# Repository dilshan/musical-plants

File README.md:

# CoCA Emerge + Tech - Musical plants project

[CoCA](http://www.cocaartists.com) "Emerge + Tech" - Musical plants is an electronics, software and plants base exhibit we initially developed for [Cinnamon Colomboscope](http://www.cinnamoncolomboscope.com/) 2016 exhibition. This installation will feature a touch sensitive sensor that will generate a soothing sound from each plant. By interacting with individual plants, the audience can create musical compositions.

Sensor unit of this project consists with 14 high sensitive, configurable voltage detectors and USB interface. In this sensor unit we use Samsung's KA2284 as amplifier, level detector, and PIC18F4550 8-bit MCU as data multiplexer and USB I/O controller. PC817 opto isolators are used to interface between analog front-end and digital data processor. In this design both analog and digital circuits are physically and electronically isolated to minimize the noises and interferences.

### Compiling source code

PC application of this project is developed by using [HIDAPI](https://github.com/signal11/hidapi) and [irrKlang](http://www.ambiera.com/irrklang) libraries. This application is designed to work with <I>Microsoft Windows</I> operating systems and we tested it on Windows 7 and Windows 10. 

PC application of this project is developed using <I>Microsoft Visual C++ 2015</I> edition. To compile the application <I>HIDAPI</I> and <I>irrKlang</I> source codes and libraries are need to copy into \frontend directory. 

PIC18F4550 firmware is developed using <I>MikroElektronika's mikroC PRO for PIC</I> compiler. Recommended MCU configuration register values for this firmware is listed in below:

* PLL prescaler : /5 (20 MHz)
* System clock postscaler : /2 (/1)
* USB clock : 96 MHz PLL /2
* Osciliator : HSPLL
* Fail safe clock monitor : OFF
* Internal external switching : OFF
* Power-up timer : OFF
* Brown-out reset : OFF
* Brown-out reset voltage : 2.0V
* USB voltage regulator : ON
* Watchdog timer : OFF
* Watchdog timer postscaler : 1:32768
* CCP2 multiplexed with : RC1
* PortB reset state : Digital
* Low power timer 1 osc : High power
* MCLR pin : Reset
* Stack overflow / underflow : ON
* In-circuit port : OFF
* Enhanced CPU : OFF
* Boot block : OPEN
* Code lock : OPEN
* Data EEPROM : OPEN
* Table write boot block : OPEN
* Table write code : OPEN
* Table read boot block : OPEN
* Table read code : OPEN

### Licenses

All the audio clips used in this project are produced by using xylophone and released under the terms of [Creative Commons Attribution-ShareAlike 4.0 International License](https://creativecommons.org/licenses/by-sa/4.0) (CC BY-SA 4.0).

This musical plants project is an open source hardware project and all the source codes and compiled binaries are released under the [MIT Licenses](https://opensource.org/licenses/MIT).

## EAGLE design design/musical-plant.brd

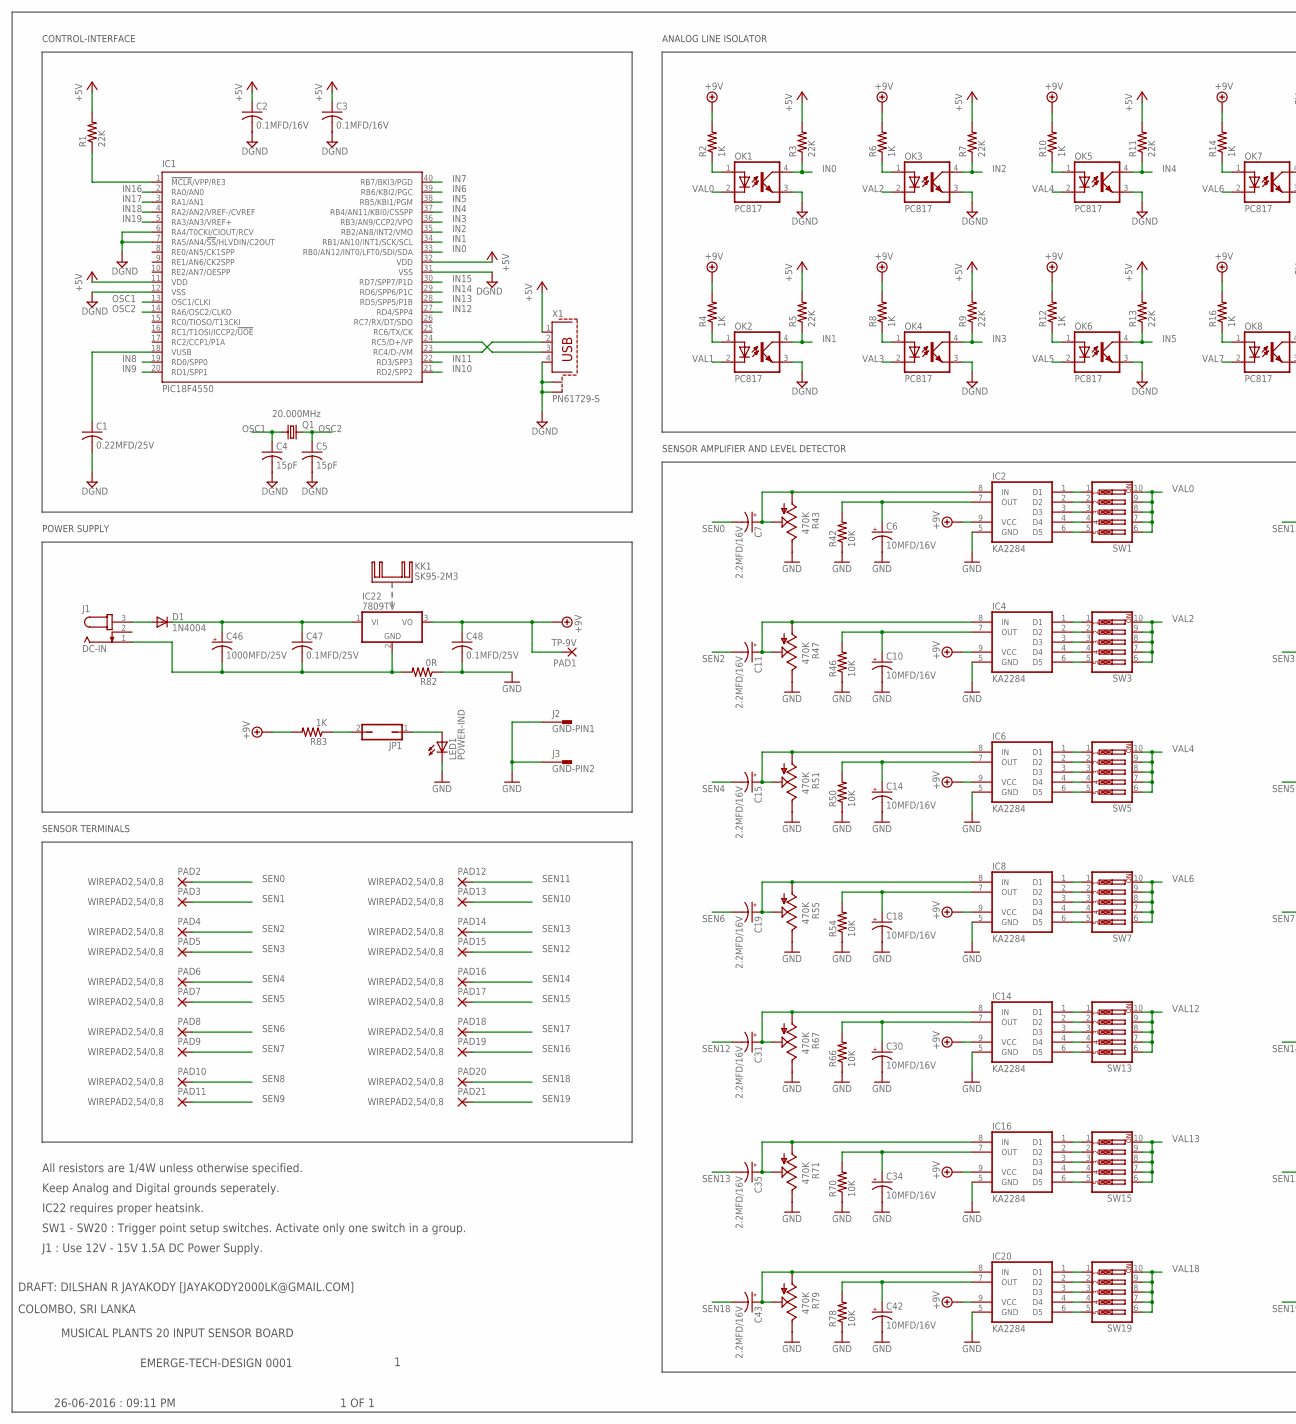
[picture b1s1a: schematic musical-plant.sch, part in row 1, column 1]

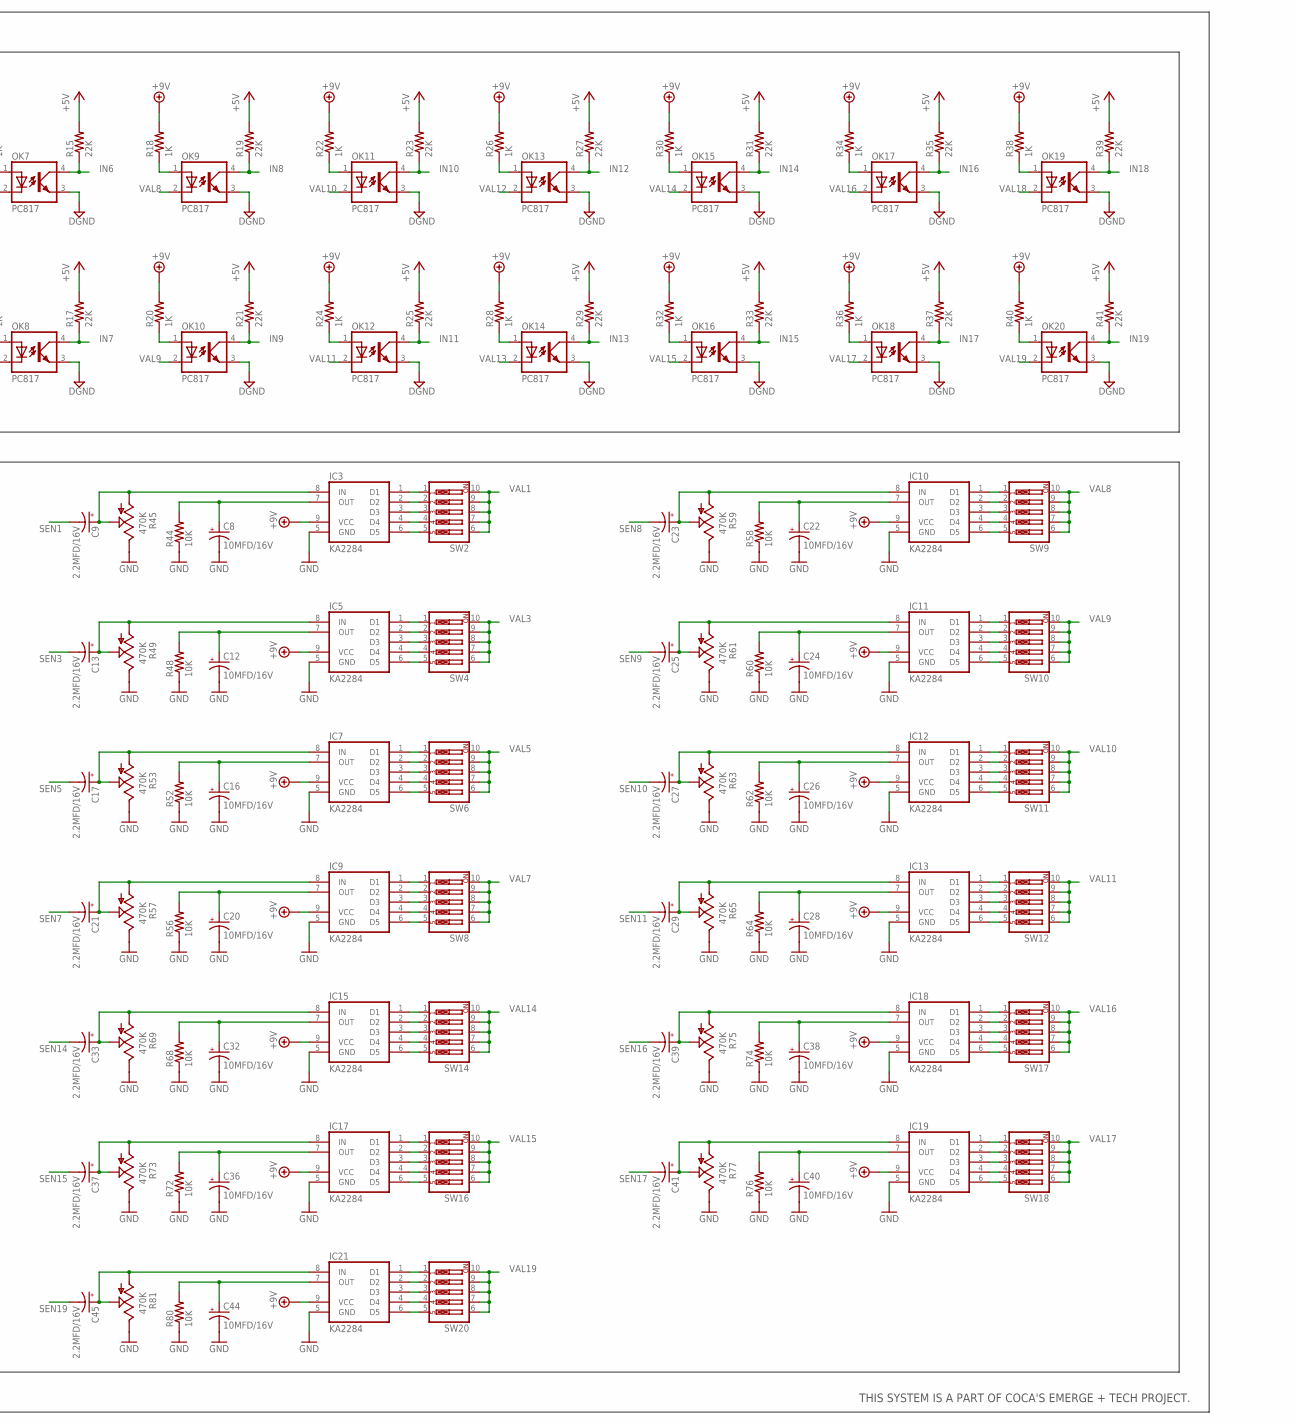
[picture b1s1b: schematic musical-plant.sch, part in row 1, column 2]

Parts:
C1: 0.22MFD/25V; C075-052X106
C2, C3: 0.1MFD/16V; C050-030X075
C4, C5: 15pF; C025-025X050
C6, C8, C10, C12, C14, C16, C18, C20, C22, C24, C26, C28, C30, C32, C34, C36, C38, C40, C42, C44: 10MFD/16V; E2,5-6E
C7, C9, C11, C13, C15, C17, C19, C21, C23, C25, C27, C29, C31, C33, C35, C37, C39, C41, C43, C45: 2.2MFD/16V; E2,5-6E
C46: 1000MFD/25V; E5-13
C47, C48: 0.1MFD/25V; C075-052X106
D1: 1N4004; DO41-10
IC1: PIC18F4550; DIL40
IC2, IC3, IC4, IC5, IC6, IC7, IC8, IC9, IC10, IC11, IC12, IC13, IC14, IC15, IC16, IC17, IC18, IC19, IC20, IC21: KA2284; SIP-9
IC22: 7809TV; TO220V
J1: DC-IN; SPC4078
J2: GND-PIN1; F061.080
J3: GND-PIN2; F061.080
JP1: JP1Q; JP1
KK1: SK95-2M3
LED1: POWER-IND; LED3MM
OK1, OK2, OK3, OK4, OK5, OK6, OK7, OK8, OK9, OK10, OK11, OK12, OK13, OK14, OK15, OK16, OK17, OK18, OK19, OK20: PC817; DIL04
PAD1: TP-9V; 2,15/1,0
PAD2, PAD3, PAD4, PAD5, PAD6, PAD7, PAD8, PAD9, PAD10, PAD11, PAD12, PAD13, PAD14, PAD15, PAD16, PAD17, PAD18, PAD19, PAD20, PAD21: WIREPAD2,54/0,8; 2,54/0,8
Q1: 20.000MHz; HC49/S
R1: 22K; 0207/10
R2, R4, R6, R8, R10, R12, R14, R16, R18, R20, R22, R24, R26, R28, R30, R32, R34, R36, R38, R40, R83: 1K; 0207/10
R3, R5, R7, R9, R11, R13, R15, R17, R19, R21, R23, R25, R27, R29, R31, R33, R35, R37, R39, R41: 22K; 0207/15
R42, R44, R46, R48, R50, R52, R54, R56, R58, R60, R62, R64, R66, R68, R70, R72, R74, R76, R78, R80: 10K; 0207/10
R43, R45, R47, R49, R51, R53, R55, R57, R59, R61, R63, R65, R67, R69, R71, R73, R75, R77, R79, R81: 470K; RS3
R82: 0R; 0207/10
SW1, SW2, SW3, SW4, SW5, SW6, SW7, SW8, SW9, SW10, SW11, SW12, SW13, SW14, SW15, SW16, SW17, SW18, SW19, SW20: SW_DIP-5; EDG-05
X1: PN61729-S

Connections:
+5V: C2.1, C3.1, IC1.11 (VDD), IC1.32 (VDD), R1.2, R3.2, R5.2, R7.2, R9.2, R11.2, R13.2, R15.2, R17.2, R19.2, R21.2, R23.2, R25.2, R27.2, R29.2, R31.2, R33.2, R35.2, R37.2, R39.2, R41.2, X1.1
+9V: C48.1, IC2.9 (VCC), IC3.9 (VCC), IC4.9 (VCC), IC5.9 (VCC), IC6.9 (VCC), IC7.9 (VCC), IC8.9 (VCC), IC9.9 (VCC), IC10.9 (VCC), IC11.9 (VCC), IC12.9 (VCC), IC13.9 (VCC), IC14.9 (VCC), IC15.9 (VCC), IC16.9 (VCC), IC17.9 (VCC), IC18.9 (VCC), IC19.9 (VCC), IC20.9 (VCC), IC21.9 (VCC), IC22.3 (VO), PAD1.1, R2.2, R4.2, R6.2, R8.2, R10.2, R12.2, R14.2, R16.2, R18.2, R20.2, R22.2, R24.2, R26.2, R28.2, R30.2, R32.2, R34.2, R36.2, R38.2, R40.2, R83.2
D-MINUS: IC1.23 (RC4/D-/VM), X1.2
D-PLUS: IC1.24 (RC5/D+/VP), X1.3
DGND: C1.2, C2.2, C3.2, C4.2, C5.2, IC1.6 (RA4/T0CKI/CIOUT/RCV), IC1.7 (RA5/AN4/!SS!/HLVDIN/C2OUT), IC1.12 (VSS), IC1.31 (VSS), OK1.3 (EMIT), OK2.3 (EMIT), OK3.3 (EMIT), OK4.3 (EMIT), OK5.3 (EMIT), OK6.3 (EMIT), OK7.3 (EMIT), OK8.3 (EMIT), OK9.3 (EMIT), OK10.3 (EMIT), OK11.3 (EMIT), OK12.3 (EMIT), OK13.3 (EMIT), OK14.3 (EMIT), OK15.3 (EMIT), OK16.3 (EMIT), OK17.3 (EMIT), OK18.3 (EMIT), OK19.3 (EMIT), OK20.3 (EMIT), X1.4, X1.S1, X1.S2
GND: C6.-, C8.-, C10.-, C12.-, C14.-, C16.-, C18.-, C20.-, C22.-, C24.-, C26.-, C28.-, C30.-, C32.-, C34.-, C36.-, C38.-, C40.-, C42.-, C44.-, C48.2, IC2.5 (GND), IC3.5 (GND), IC4.5 (GND), IC5.5 (GND), IC6.5 (GND), IC7.5 (GND), IC8.5 (GND), IC9.5 (GND), IC10.5 (GND), IC11.5 (GND), IC12.5 (GND), IC13.5 (GND), IC14.5 (GND), IC15.5 (GND), IC16.5 (GND), IC17.5 (GND), IC18.5 (GND), IC19.5 (GND), IC20.5 (GND), IC21.5 (GND), J2.1A, J2.1B, J3.1A, J3.1B, LED1.K (C), R42.1, R43.E, R44.1, R45.E, R46.1, R47.E, R48.1, R49.E, R50.1, R51.E, R52.1, R53.E, R54.1, R55.E, R56.1, R57.E, R58.1, R59.E, R60.1, R61.E, R62.1, R63.E, R64.1, R65.E, R66.1, R67.E, R68.1, R69.E, R70.1, R71.E, R72.1, R73.E, R74.1, R75.E, R76.1, R77.E, R78.1, R79.E, R80.1, R81.E, R82.1
IN0: IC1.33 (RB0/AN12/INT0/LFT0/SDI/SDA), OK1.4 (COL), R3.1
IN1: IC1.34 (RB1/AN10/INT1/SCK/SCL), OK2.4 (COL), R5.1
IN2: IC1.35 (RB2/AN8/INT2/VMO), OK3.4 (COL), R7.1
IN3: IC1.36 (RB3/AN9/CCP2/VPO), OK4.4 (COL), R9.1
IN4: IC1.37 (RB4/AN11/KBI0/CSSPP), OK5.4 (COL), R11.1
IN5: IC1.38 (RB5/KBI1/PGM), OK6.4 (COL), R13.1
IN6: IC1.39 (RB6/KBI2/PGC), OK7.4 (COL), R15.1
IN7: IC1.40 (RB7/BKI3/PGD), OK8.4 (COL), R17.1
IN8: IC1.19 (RD0/SPP0), OK9.4 (COL), R19.1
IN9: IC1.20 (RD1/SPP1), OK10.4 (COL), R21.1
IN10: IC1.21 (RD2/SPP2), OK11.4 (COL), R23.1
IN11: IC1.22 (RD3/SPP3), OK12.4 (COL), R25.1
IN12: IC1.27 (RD4/SPP4), OK13.4 (COL), R27.1
IN13: IC1.28 (RD5/SPP5/P1B), OK14.4 (COL), R29.1
IN14: IC1.29 (RD6/SPP6/P1C), OK15.4 (COL), R31.1
IN15: IC1.30 (RD7/SPP7/P1D), OK16.4 (COL), R33.1
IN16: IC1.2 (RA0/AN0), OK17.4 (COL), R35.1
IN17: IC1.3 (RA1/AN1), OK18.4 (COL), R37.1
IN18: IC1.4 (RA2/AN2/VREF-/CVREF), OK19.4 (COL), R39.1
IN19: IC1.5 (RA3/AN3/VREF+), OK20.4 (COL), R41.1
MCLR: IC1.1 (!MCLR!/VPP/RE3), R1.1
unnamed: OK1.1 (A), R2.1
unnamed: OK2.1 (A), R4.1
unnamed: OK3.1 (A), R6.1
unnamed: OK4.1 (A), R8.1
unnamed: OK5.1 (A), R10.1
unnamed: OK6.1 (A), R12.1
unnamed: OK7.1 (A), R14.1
unnamed: OK8.1 (A), R16.1
unnamed: OK9.1 (A), R18.1
unnamed: OK10.1 (A), R20.1
unnamed: OK11.1 (A), R22.1
unnamed: OK12.1 (A), R24.1
unnamed: OK13.1 (A), R26.1
unnamed: OK14.1 (A), R28.1
unnamed: OK15.1 (A), R30.1
unnamed: OK16.1 (A), R32.1
unnamed: OK17.1 (A), R34.1
unnamed: OK18.1 (A), R36.1
unnamed: OK19.1 (A), R38.1
unnamed: OK20.1 (A), R40.1
unnamed: IC2.1 (D1), SW1.1
unnamed: IC2.2 (D2), SW1.2
unnamed: IC2.3 (D3), SW1.3
unnamed: IC2.4 (D4), SW1.4
unnamed: IC2.6 (D5), SW1.5
unnamed: C6.+, IC2.7 (OUT), R42.2
unnamed: C7.+, IC2.8 (IN), R43.A, R43.S
unnamed: IC3.1 (D1), SW2.1
unnamed: IC3.2 (D2), SW2.2
unnamed: IC3.3 (D3), SW2.3
unnamed: IC3.4 (D4), SW2.4
unnamed: IC3.6 (D5), SW2.5
unnamed: C8.+, IC3.7 (OUT), R44.2
unnamed: C9.+, IC3.8 (IN), R45.A, R45.S
unnamed: IC4.1 (D1), SW3.1
unnamed: IC4.2 (D2), SW3.2
unnamed: IC4.3 (D3), SW3.3
unnamed: IC4.4 (D4), SW3.4
unnamed: IC4.6 (D5), SW3.5
unnamed: C10.+, IC4.7 (OUT), R46.2
unnamed: C11.+, IC4.8 (IN), R47.A, R47.S
unnamed: IC5.1 (D1), SW4.1
unnamed: IC5.2 (D2), SW4.2
unnamed: IC5.3 (D3), SW4.3
unnamed: IC5.4 (D4), SW4.4
unnamed: IC5.6 (D5), SW4.5
unnamed: C12.+, IC5.7 (OUT), R48.2
unnamed: C13.+, IC5.8 (IN), R49.A, R49.S
unnamed: IC6.1 (D1), SW5.1
unnamed: IC6.2 (D2), SW5.2
unnamed: IC6.3 (D3), SW5.3
unnamed: IC6.4 (D4), SW5.4
unnamed: IC6.6 (D5), SW5.5
unnamed: C14.+, IC6.7 (OUT), R50.2
unnamed: C15.+, IC6.8 (IN), R51.A, R51.S
unnamed: IC7.1 (D1), SW6.1
unnamed: IC7.2 (D2), SW6.2
unnamed: IC7.3 (D3), SW6.3
unnamed: IC7.4 (D4), SW6.4
unnamed: IC7.6 (D5), SW6.5
unnamed: C16.+, IC7.7 (OUT), R52.2
unnamed: C17.+, IC7.8 (IN), R53.A, R53.S
unnamed: IC8.1 (D1), SW7.1
unnamed: IC8.2 (D2), SW7.2
unnamed: IC8.3 (D3), SW7.3
unnamed: IC8.4 (D4), SW7.4
unnamed: IC8.6 (D5), SW7.5
unnamed: C18.+, IC8.7 (OUT), R54.2
unnamed: C19.+, IC8.8 (IN), R55.A, R55.S
unnamed: IC9.1 (D1), SW8.1
unnamed: IC9.2 (D2), SW8.2
unnamed: IC9.3 (D3), SW8.3
unnamed: IC9.4 (D4), SW8.4
unnamed: IC9.6 (D5), SW8.5
unnamed: C20.+, IC9.7 (OUT), R56.2
unnamed: C21.+, IC9.8 (IN), R57.A, R57.S
unnamed: IC10.1 (D1), SW9.1
unnamed: IC10.2 (D2), SW9.2
unnamed: IC10.3 (D3), SW9.3
unnamed: IC10.4 (D4), SW9.4
unnamed: IC10.6 (D5), SW9.5
unnamed: C22.+, IC10.7 (OUT), R58.2
unnamed: C23.+, IC10.8 (IN), R59.A, R59.S
unnamed: IC11.1 (D1), SW10.1
unnamed: IC11.2 (D2), SW10.2
unnamed: IC11.3 (D3), SW10.3
unnamed: IC11.4 (D4), SW10.4
unnamed: IC11.6 (D5), SW10.5
unnamed: C24.+, IC11.7 (OUT), R60.2
unnamed: C25.+, IC11.8 (IN), R61.A, R61.S
unnamed: IC12.1 (D1), SW11.1
unnamed: IC12.2 (D2), SW11.2
unnamed: IC12.3 (D3), SW11.3
unnamed: IC12.4 (D4), SW11.4
unnamed: IC12.6 (D5), SW11.5
unnamed: C26.+, IC12.7 (OUT), R62.2
unnamed: C27.+, IC12.8 (IN), R63.A, R63.S
unnamed: IC13.1 (D1), SW12.1
unnamed: IC13.2 (D2), SW12.2
unnamed: IC13.3 (D3), SW12.3
unnamed: IC13.4 (D4), SW12.4
unnamed: IC13.6 (D5), SW12.5
unnamed: C28.+, IC13.7 (OUT), R64.2
unnamed: C29.+, IC13.8 (IN), R65.A, R65.S
unnamed: IC14.1 (D1), SW13.1
unnamed: IC14.2 (D2), SW13.2
unnamed: IC14.3 (D3), SW13.3
unnamed: IC14.4 (D4), SW13.4
unnamed: IC14.6 (D5), SW13.5
unnamed: C30.+, IC14.7 (OUT), R66.2
unnamed: C31.+, IC14.8 (IN), R67.A, R67.S
unnamed: IC15.1 (D1), SW14.1
unnamed: IC15.2 (D2), SW14.2
unnamed: IC15.3 (D3), SW14.3
unnamed: IC15.4 (D4), SW14.4
unnamed: IC15.6 (D5), SW14.5
unnamed: C32.+, IC15.7 (OUT), R68.2
unnamed: C33.+, IC15.8 (IN), R69.A, R69.S
unnamed: IC16.1 (D1), SW15.1
unnamed: IC16.2 (D2), SW15.2
unnamed: IC16.3 (D3), SW15.3
unnamed: IC16.4 (D4), SW15.4
unnamed: IC16.6 (D5), SW15.5
unnamed: C34.+, IC16.7 (OUT), R70.2
unnamed: C35.+, IC16.8 (IN), R71.A, R71.S
unnamed: IC17.1 (D1), SW16.1
unnamed: IC17.2 (D2), SW16.2
unnamed: IC17.3 (D3), SW16.3
unnamed: IC17.4 (D4), SW16.4
unnamed: IC17.6 (D5), SW16.5
unnamed: C36.+, IC17.7 (OUT), R72.2
unnamed: C37.+, IC17.8 (IN), R73.A, R73.S
unnamed: IC18.1 (D1), SW17.1
unnamed: IC18.2 (D2), SW17.2
unnamed: IC18.3 (D3), SW17.3
unnamed: IC18.4 (D4), SW17.4
unnamed: IC18.6 (D5), SW17.5
unnamed: C38.+, IC18.7 (OUT), R74.2
unnamed: C39.+, IC18.8 (IN), R75.A, R75.S
unnamed: IC19.1 (D1), SW18.1
unnamed: IC19.2 (D2), SW18.2
unnamed: IC19.3 (D3), SW18.3
unnamed: IC19.4 (D4), SW18.4
unnamed: IC19.6 (D5), SW18.5
unnamed: C40.+, IC19.7 (OUT), R76.2
unnamed: C41.+, IC19.8 (IN), R77.A, R77.S
unnamed: IC20.1 (D1), SW19.1
unnamed: IC20.2 (D2), SW19.2
unnamed: IC20.3 (D3), SW19.3
unnamed: IC20.4 (D4), SW19.4
unnamed: IC20.6 (D5), SW19.5
unnamed: C42.+, IC20.7 (OUT), R78.2
unnamed: C43.+, IC20.8 (IN), R79.A, R79.S
unnamed: IC21.1 (D1), SW20.1
unnamed: IC21.2 (D2), SW20.2
unnamed: IC21.3 (D3), SW20.3
unnamed: IC21.4 (D4), SW20.4
unnamed: IC21.6 (D5), SW20.5
unnamed: C44.+, IC21.7 (OUT), R80.2
unnamed: C45.+, IC21.8 (IN), R81.A, R81.S
unnamed: D1.A, J1.3
unnamed: C46.+, C47.1, D1.C, IC22.1 (VI)
unnamed: C46.-, C47.2, IC22.2 (GND), J1.1, R82.2
unnamed: JP1.1, LED1.A
unnamed: JP1.2, R83.1
OSC1: C4.1, IC1.13 (OSC1/CLKI), Q1.1
OSC2: C5.1, IC1.14 (RA6/OSC2/CLKO), Q1.2
SEN0: C7.-, PAD2.1
SEN1: C9.-, PAD3.1
SEN2: C11.-, PAD4.1
SEN3: C13.-, PAD5.1
SEN4: C15.-, PAD6.1
SEN5: C17.-, PAD7.1
SEN6: C19.-, PAD8.1
SEN7: C21.-, PAD9.1
SEN8: C23.-, PAD10.1
SEN9: C25.-, PAD11.1
SEN10: C27.-, PAD13.1
SEN11: C29.-, PAD12.1
SEN12: C31.-, PAD15.1
SEN13: C35.-, PAD14.1
SEN14: C33.-, PAD16.1
SEN15: C37.-, PAD17.1
SEN16: C39.-, PAD19.1
SEN17: C41.-, PAD18.1
SEN18: C43.-, PAD20.1
SEN19: C45.-, PAD21.1
VAL0: OK1.2 (C), SW1.6, SW1.7, SW1.8, SW1.9, SW1.10
VAL1: OK2.2 (C), SW2.6, SW2.7, SW2.8, SW2.9, SW2.10
VAL2: OK3.2 (C), SW3.6, SW3.7, SW3.8, SW3.9, SW3.10
VAL3: OK4.2 (C), SW4.6, SW4.7, SW4.8, SW4.9, SW4.10
VAL4: OK5.2 (C), SW5.6, SW5.7, SW5.8, SW5.9, SW5.10
VAL5: OK6.2 (C), SW6.6, SW6.7, SW6.8, SW6.9, SW6.10
VAL6: OK7.2 (C), SW7.6, SW7.7, SW7.8, SW7.9, SW7.10
VAL7: OK8.2 (C), SW8.6, SW8.7, SW8.8, SW8.9, SW8.10
VAL8: OK9.2 (C), SW9.6, SW9.7, SW9.8, SW9.9, SW9.10
VAL9: OK10.2 (C), SW10.6, SW10.7, SW10.8, SW10.9, SW10.10
VAL10: OK11.2 (C), SW11.6, SW11.7, SW11.8, SW11.9, SW11.10
VAL11: OK12.2 (C), SW12.6, SW12.7, SW12.8, SW12.9, SW12.10
VAL12: OK13.2 (C), SW13.6, SW13.7, SW13.8, SW13.9, SW13.10
VAL13: OK14.2 (C), SW15.6, SW15.7, SW15.8, SW15.9, SW15.10
VAL14: OK15.2 (C), SW14.6, SW14.7, SW14.8, SW14.9, SW14.10
VAL15: OK16.2 (C), SW16.6, SW16.7, SW16.8, SW16.9, SW16.10
VAL16: OK17.2 (C), SW17.6, SW17.7, SW17.8, SW17.9, SW17.10
VAL17: OK18.2 (C), SW18.6, SW18.7, SW18.8, SW18.9, SW18.10
VAL18: OK19.2 (C), SW19.6, SW19.7, SW19.8, SW19.9, SW19.10
VAL19: OK20.2 (C), SW20.6, SW20.7, SW20.8, SW20.9, SW20.10
VUSB: C1.1, IC1.18 (VUSB)

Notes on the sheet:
CONTROL-INTERFACE
ANALOG LINE ISOLATOR
SENSOR AMPLIFIER AND LEVEL DETECTOR
POWER SUPPLY
SENSOR TERMINALS
MUSICAL PLANTS 20 INPUT SENSOR BOARD
EMERGE-TECH-DESIGN 0001
1 OF 1
26-06-2016 : 09:11 PM
DRAFT: DILSHAN R JAYAKODY [JAYAKODY2000LK@GMAIL.COM]
COLOMBO, SRI LANKA
All resistors are 1/4W unless otherwise specified.
Keep Analog and Digital grounds seperately.
IC22 requires proper heatsink.
SW1 - SW20 : Trigger point setup switches. Activate only one switch in a group.
J1 : Use 12V - 15V 1.5A DC Power Supply.
THIS SYSTEM IS A PART OF COCA'S EMERGE + TECH PROJECT.

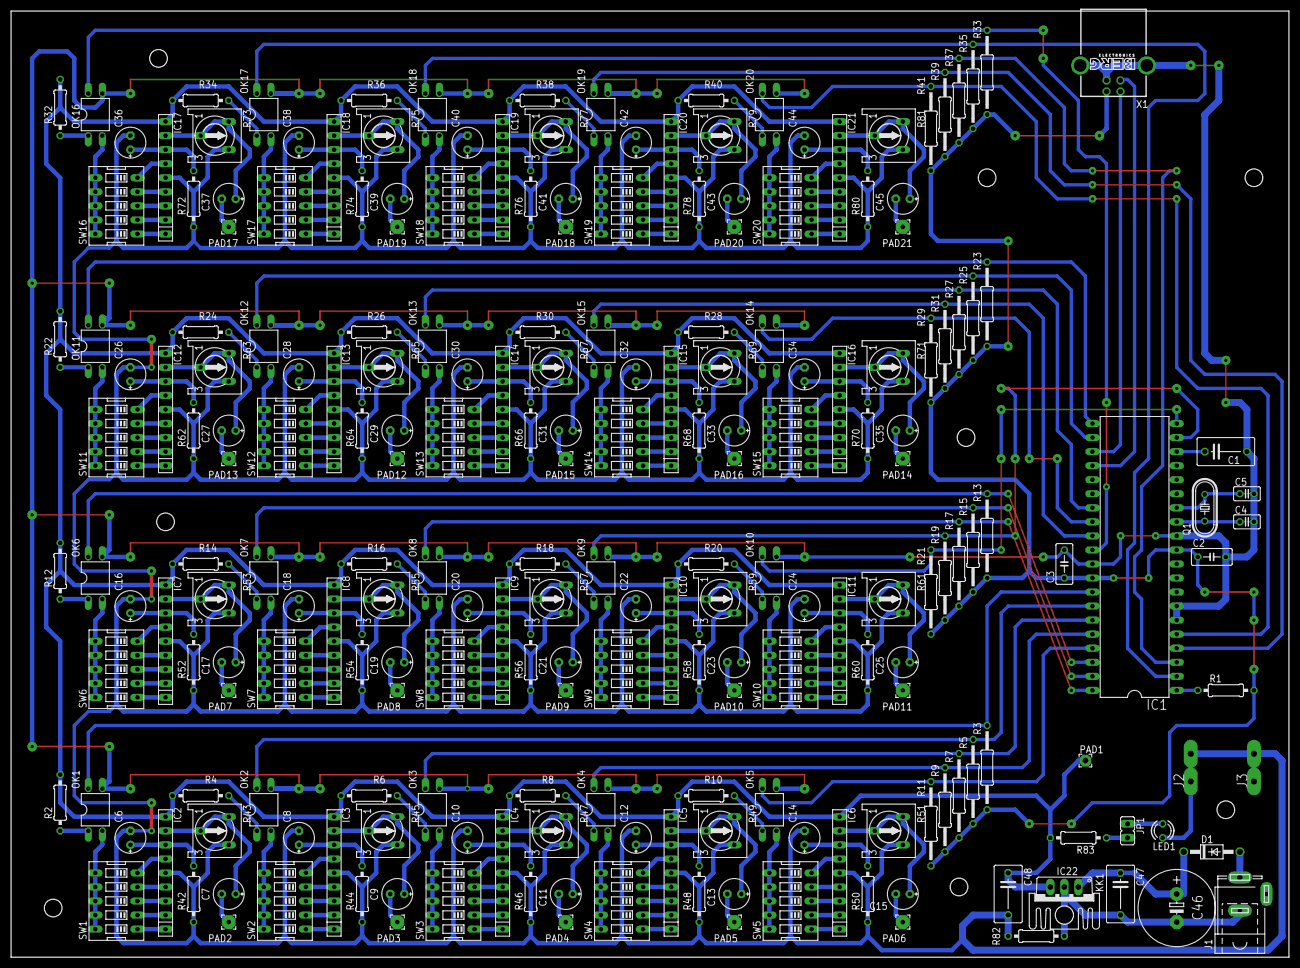
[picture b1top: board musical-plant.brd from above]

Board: 2 copper layers, 231.1 x 171.1 mm, 223 parts (0 on the bottom side), 235 nets.

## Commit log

2016-08-30 Initial project version.
2016-08-30 Update MCU configuration register values in project readme file.
2016-08-30 Group documentation content.
